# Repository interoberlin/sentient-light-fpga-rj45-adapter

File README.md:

# Lattice iCEstick adapter with four RJ-45 sockets

The adapter in this repository takes sixteen 3V3 logic level input signals,
converts them to 5V and outputs them on four RJ-45 sockets, four signals per socket,
one signal per twisted pair of an off-the-shelf CAT-5 ethernet cable.
Eight additional inputs can switch the RJ-45 sockets' LEDs on and off.

## Pictures

### Top layer

### Bottom layer

### With components

### With iCEstick

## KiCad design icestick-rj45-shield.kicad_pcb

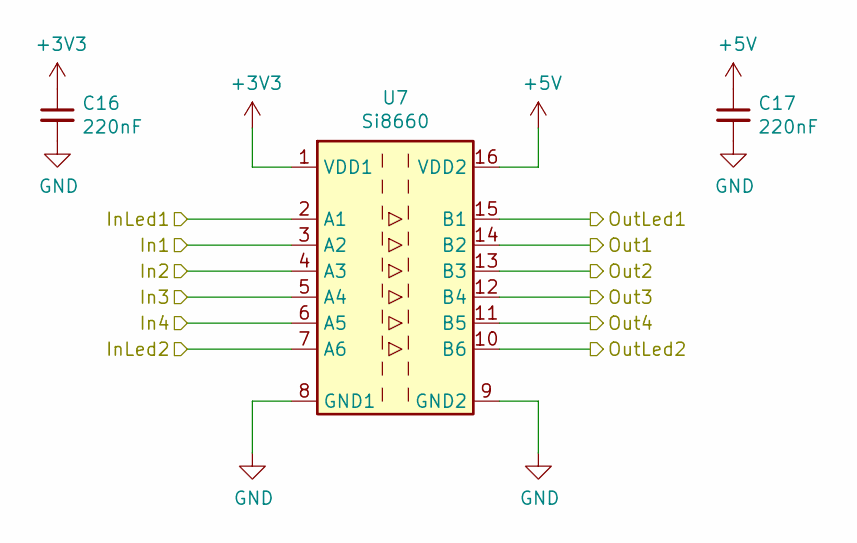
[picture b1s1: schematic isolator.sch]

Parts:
C1, C2: 220nF; C_0805_2012Metric_Pad1.15x1.40mm_HandSolder
U1: Si8660; SOIC-16_3.9x9.9mm_P1.27mm

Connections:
+3V3: C1.1, U1.1 (VDD1); also elsewhere on the board
+5V: C2.1, U1.16 (VDD2); also elsewhere on the board
/Connector 1/LED1: U1.10 (B6); also elsewhere on the board
/Connector 1/LED2: U1.15 (B1); also elsewhere on the board
/Isolator 1/Out1: U1.14 (B2); also elsewhere on the board
/Isolator 1/Out2: U1.13 (B3); also elsewhere on the board
/Isolator 1/Out3: U1.12 (B4); also elsewhere on the board
/Isolator 1/Out4: U1.11 (B5); also elsewhere on the board
/iCEstick connector/FPGA_114: U1.7 (A6); also elsewhere on the board
/iCEstick connector/FPGA_115: U1.6 (A5); also elsewhere on the board
/iCEstick connector/FPGA_116: U1.5 (A4); also elsewhere on the board
/iCEstick connector/FPGA_117: U1.4 (A3); also elsewhere on the board
/iCEstick connector/FPGA_118: U1.3 (A2); also elsewhere on the board
/iCEstick connector/FPGA_119: U1.2 (A1); also elsewhere on the board
GND: C1.2, C2.2, U1.8 (GND1), U1.9 (GND2); also elsewhere on the board

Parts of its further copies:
C12, C13, C14, C15, C16, C17: 220nF; C_0805_2012Metric_Pad1.15x1.40mm_HandSolder
U5, U6, U7: Si8660; SOIC-16_3.9x9.9mm_P1.27mm

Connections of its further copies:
+3V3: C12.1, C14.1, C16.1, U5.1 (VDD1), U6.1 (VDD1), U7.1 (VDD1); also elsewhere on the board
+5V: C13.1, C15.1, C17.1, U5.16 (VDD2), U6.16 (VDD2), U7.16 (VDD2); also elsewhere on the board
/Connector 2/LED1: U5.10 (B6); also elsewhere on the board
/Connector 2/LED2: U5.15 (B1); also elsewhere on the board
/Connector 3/LED1: U7.10 (B6); also elsewhere on the board
/Connector 3/LED2: U7.15 (B1); also elsewhere on the board
/Connector 4/LED1: U6.10 (B6); also elsewhere on the board
/Connector 4/LED2: U6.15 (B1); also elsewhere on the board
/Isolator 2/Out1: U5.14 (B2); also elsewhere on the board
/Isolator 2/Out2: U5.13 (B3); also elsewhere on the board
/Isolator 2/Out3: U5.12 (B4); also elsewhere on the board
/Isolator 2/Out4: U5.11 (B5); also elsewhere on the board
/Isolator 3/Out1: U7.14 (B2); also elsewhere on the board
/Isolator 3/Out2: U7.13 (B3); also elsewhere on the board
/Isolator 3/Out3: U7.12 (B4); also elsewhere on the board
/Isolator 3/Out4: U7.11 (B5); also elsewhere on the board
/Isolator 4/Out1: U6.14 (B2); also elsewhere on the board
/Isolator 4/Out2: U6.13 (B3); also elsewhere on the board
/Isolator 4/Out3: U6.12 (B4); also elsewhere on the board
/Isolator 4/Out4: U6.11 (B5); also elsewhere on the board
/iCEstick connector/FPGA_44: U6.7 (A6); also elsewhere on the board
/iCEstick connector/FPGA_45: U6.6 (A5); also elsewhere on the board
/iCEstick connector/FPGA_47: U6.5 (A4); also elsewhere on the board
/iCEstick connector/FPGA_48: U6.4 (A3); also elsewhere on the board
/iCEstick connector/FPGA_56: U6.3 (A2); also elsewhere on the board
/iCEstick connector/FPGA_60: U6.2 (A1); also elsewhere on the board
/iCEstick connector/FPGA_61: U7.7 (A6); also elsewhere on the board
/iCEstick connector/FPGA_62: U7.6 (A5); also elsewhere on the board
/iCEstick connector/FPGA_78: U7.3 (A2); also elsewhere on the board
/iCEstick connector/FPGA_79: U7.2 (A1); also elsewhere on the board
/iCEstick connector/FPGA_80: U5.7 (A6); also elsewhere on the board
/iCEstick connector/FPGA_81: U5.6 (A5); also elsewhere on the board
/iCEstick connector/FPGA_87: U7.4 (A3); also elsewhere on the board
/iCEstick connector/FPGA_88: U7.5 (A4); also elsewhere on the board
/iCEstick connector/FPGA_90: U5.4 (A3); also elsewhere on the board
/iCEstick connector/FPGA_91: U5.5 (A4); also elsewhere on the board
/iCEstick connector/FPGA_112: U5.3 (A2); also elsewhere on the board
/iCEstick connector/FPGA_113: U5.2 (A1); also elsewhere on the board
GND: C12.2, C13.2, C14.2, C15.2, C16.2, C17.2, U5.8 (GND1), U5.9 (GND2), U6.8 (GND1), U6.9 (GND2), U7.8 (GND1), U7.9 (GND2); also elsewhere on the board

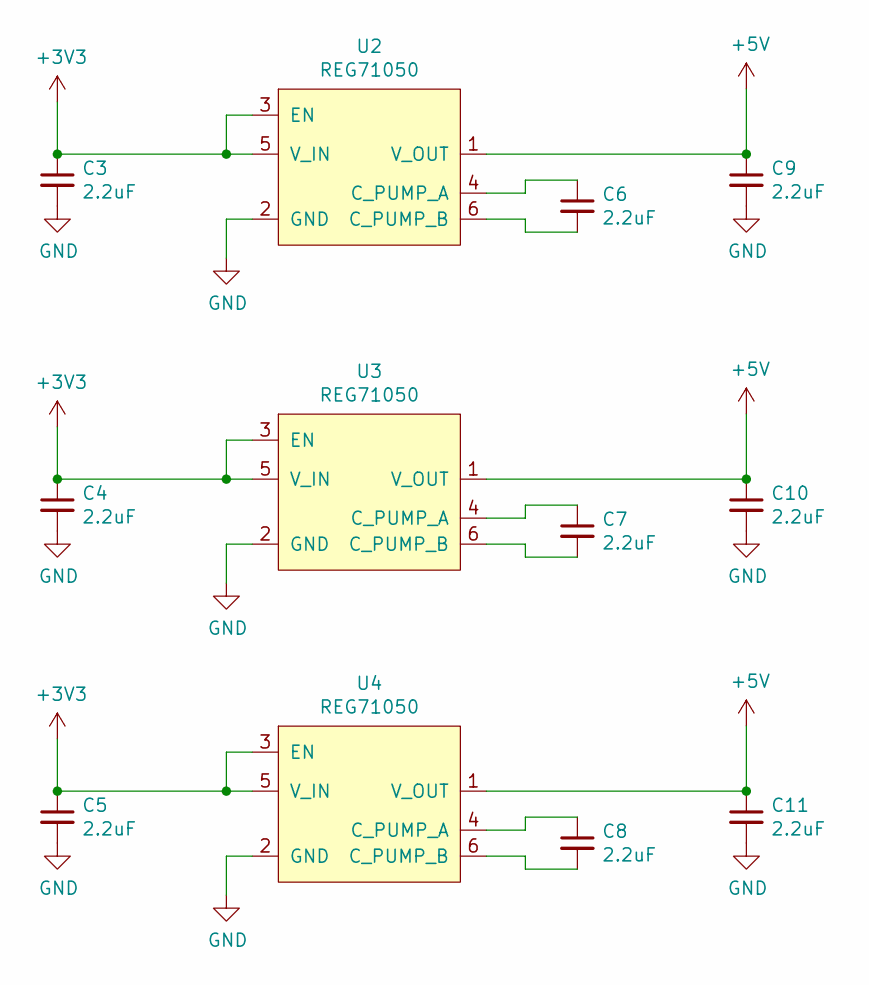
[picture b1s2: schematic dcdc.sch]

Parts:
C3, C4, C5, C6, C7, C8, C9, C10, C11: 2.2uF; C_0805_2012Metric_Pad1.15x1.40mm_HandSolder
U2, U3, U4: REG71050; SOT-23-6_Handsoldering

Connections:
+3V3: C3.1, C4.1, C5.1, U2.3 (EN), U2.5 (V_IN), U3.3 (EN), U3.5 (V_IN), U4.3 (EN), U4.5 (V_IN); also elsewhere on the board
+5V: C9.1, C10.1, C11.1, U2.1 (V_OUT), U3.1 (V_OUT), U4.1 (V_OUT); also elsewhere on the board
GND: C3.2, C4.2, C5.2, C9.2, C10.2, C11.2, U2.2 (GND), U3.2 (GND), U4.2 (GND); also elsewhere on the board
unnamed: C6.1, U2.4 (C_PUMP_A)
unnamed: C6.2, U2.6 (C_PUMP_B)
unnamed: C7.1, U3.4 (C_PUMP_A)
unnamed: C7.2, U3.6 (C_PUMP_B)
unnamed: C8.1, U4.4 (C_PUMP_A)
unnamed: C8.2, U4.6 (C_PUMP_B)

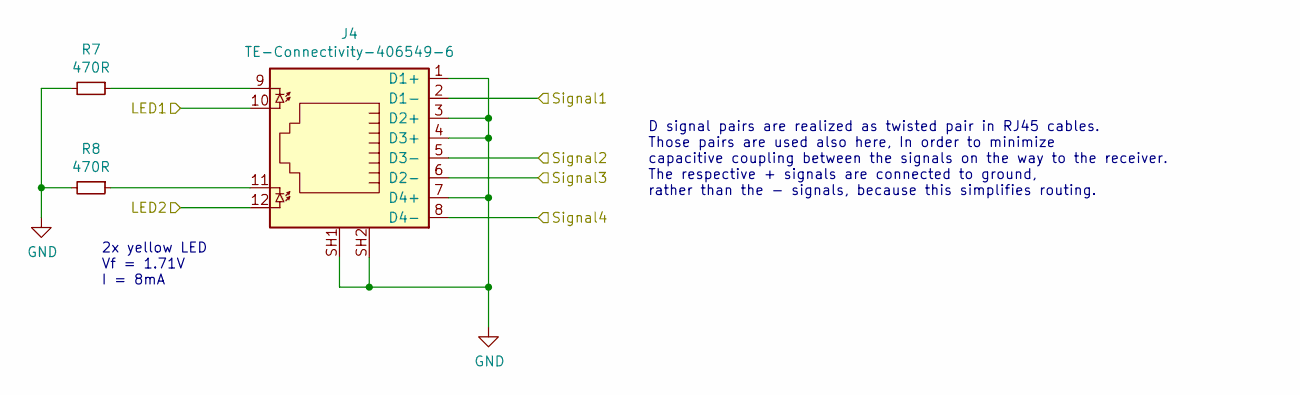
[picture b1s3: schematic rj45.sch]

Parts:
J2: TE-Connectivity-406549-6
R1, R2: 470R; R_0805_2012Metric_Pad1.15x1.40mm_HandSolder

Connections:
/Connector 2/LED1: J2.10; also elsewhere on the board
/Connector 2/LED2: J2.12; also elsewhere on the board
/Isolator 2/Out1: J2.8 (D4-); also elsewhere on the board
/Isolator 2/Out2: J2.6 (D2-); also elsewhere on the board
/Isolator 2/Out3: J2.2 (D1-); also elsewhere on the board
/Isolator 2/Out4: J2.5 (D3-); also elsewhere on the board
GND: J2.1 (D1+), J2.3 (D2+), J2.4 (D3+), J2.7 (D4+), J2.SH1, J2.SH2, R1.2, R2.2; also elsewhere on the board

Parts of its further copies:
J1, J3, J4: TE-Connectivity-406549-6
R3, R4, R5, R6, R7, R8: 470R; R_0805_2012Metric_Pad1.15x1.40mm_HandSolder

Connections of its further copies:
/Connector 1/LED1: J1.10; also elsewhere on the board
/Connector 1/LED2: J1.12; also elsewhere on the board
/Connector 3/LED1: J3.10; also elsewhere on the board
/Connector 3/LED2: J3.12; also elsewhere on the board
/Connector 4/LED1: J4.10; also elsewhere on the board
/Connector 4/LED2: J4.12; also elsewhere on the board
/Isolator 1/Out1: J1.8 (D4-); also elsewhere on the board
/Isolator 1/Out2: J1.6 (D2-); also elsewhere on the board
/Isolator 1/Out3: J1.2 (D1-); also elsewhere on the board
/Isolator 1/Out4: J1.5 (D3-); also elsewhere on the board
/Isolator 3/Out1: J3.8 (D4-); also elsewhere on the board
/Isolator 3/Out2: J3.6 (D2-); also elsewhere on the board
/Isolator 3/Out3: J3.2 (D1-); also elsewhere on the board
/Isolator 3/Out4: J3.5 (D3-); also elsewhere on the board
/Isolator 4/Out1: J4.8 (D4-); also elsewhere on the board
/Isolator 4/Out2: J4.6 (D2-); also elsewhere on the board
/Isolator 4/Out3: J4.2 (D1-); also elsewhere on the board
/Isolator 4/Out4: J4.5 (D3-); also elsewhere on the board
GND: J1.1 (D1+), J1.3 (D2+), J1.4 (D3+), J1.7 (D4+), J1.SH1, J1.SH2, J3.1 (D1+), J3.3 (D2+), J3.4 (D3+), J3.7 (D4+), J3.SH1, J3.SH2, J4.1 (D1+), J4.3 (D2+), J4.4 (D3+), J4.7 (D4+), J4.SH1, J4.SH2, R3.2, R4.2, R5.2, R6.2, R7.2, R8.2; also elsewhere on the board
unnamed: J3.9, R5.1
unnamed: J3.11, R6.1
unnamed: J4.9, R7.1
unnamed: J4.11, R8.1

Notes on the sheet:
2x yellow LED Vf = 1.71V I = 8mA
D signal pairs are realized as twisted pair in RJ45 cables. Those pairs are used also here, In order to minimize capacitive coupling between the signals on the way to the receiver. The respective + signals are connected to ground, rather than the - signals, because this simplifies routing.

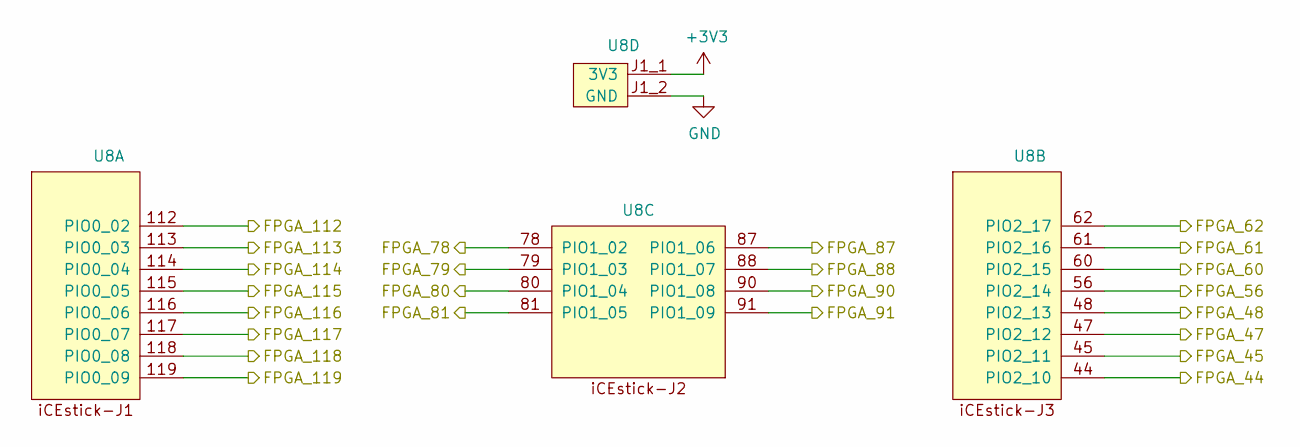
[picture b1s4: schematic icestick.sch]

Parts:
U8: iCEstick

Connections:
+3V3: U8.J1_1 (3V3), U8.J2_6 (3V3), U8.J2_12 (3V3), U8.J3_1 (3V3); also elsewhere on the board
/iCEstick connector/FPGA_44: U8.44 (PIO2_10); also elsewhere on the board
/iCEstick connector/FPGA_45: U8.45 (PIO2_11); also elsewhere on the board
/iCEstick connector/FPGA_47: U8.47 (PIO2_12); also elsewhere on the board
/iCEstick connector/FPGA_48: U8.48 (PIO2_13); also elsewhere on the board
/iCEstick connector/FPGA_56: U8.56 (PIO2_14); also elsewhere on the board
/iCEstick connector/FPGA_60: U8.60 (PIO2_15); also elsewhere on the board
/iCEstick connector/FPGA_61: U8.61 (PIO2_16); also elsewhere on the board
/iCEstick connector/FPGA_62: U8.62 (PIO2_17); also elsewhere on the board
/iCEstick connector/FPGA_78: U8.78 (PIO1_02); also elsewhere on the board
/iCEstick connector/FPGA_79: U8.79 (PIO1_03); also elsewhere on the board
/iCEstick connector/FPGA_80: U8.80 (PIO1_04); also elsewhere on the board
/iCEstick connector/FPGA_81: U8.81 (PIO1_05); also elsewhere on the board
/iCEstick connector/FPGA_87: U8.87 (PIO1_06); also elsewhere on the board
/iCEstick connector/FPGA_88: U8.88 (PIO1_07); also elsewhere on the board
/iCEstick connector/FPGA_90: U8.90 (PIO1_08); also elsewhere on the board
/iCEstick connector/FPGA_91: U8.91 (PIO1_09); also elsewhere on the board
/iCEstick connector/FPGA_112: U8.112 (PIO0_02); also elsewhere on the board
/iCEstick connector/FPGA_113: U8.113 (PIO0_03); also elsewhere on the board
/iCEstick connector/FPGA_114: U8.114 (PIO0_04); also elsewhere on the board
/iCEstick connector/FPGA_115: U8.115 (PIO0_05); also elsewhere on the board
/iCEstick connector/FPGA_116: U8.116 (PIO0_06); also elsewhere on the board
/iCEstick connector/FPGA_117: U8.117 (PIO0_07); also elsewhere on the board
/iCEstick connector/FPGA_118: U8.118 (PIO0_08); also elsewhere on the board
/iCEstick connector/FPGA_119: U8.119 (PIO0_09); also elsewhere on the board
GND: U8.J1_2 (GND), U8.J2_5 (GND), U8.J2_11 (GND), U8.J3_2 (GND); also elsewhere on the board

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
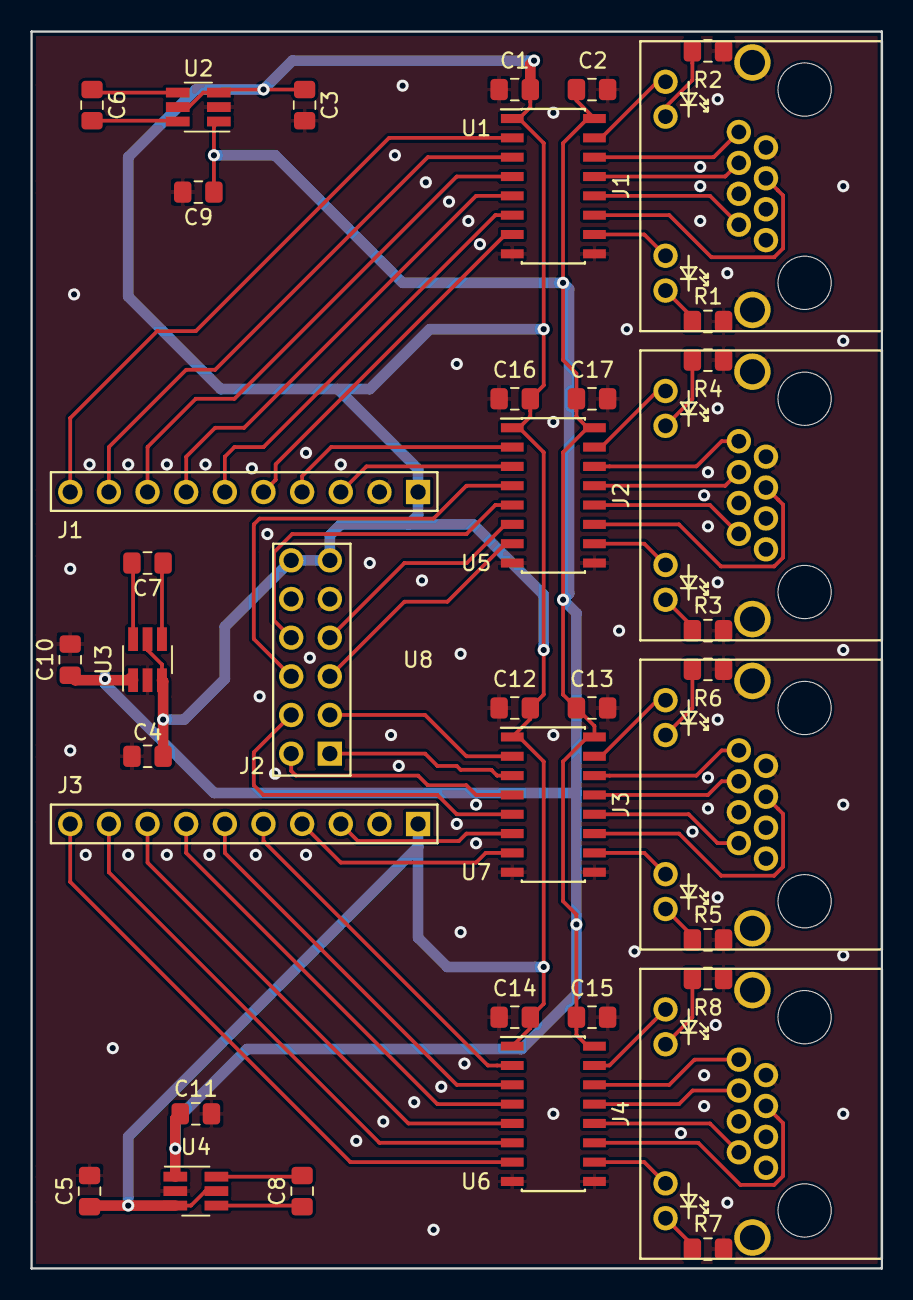
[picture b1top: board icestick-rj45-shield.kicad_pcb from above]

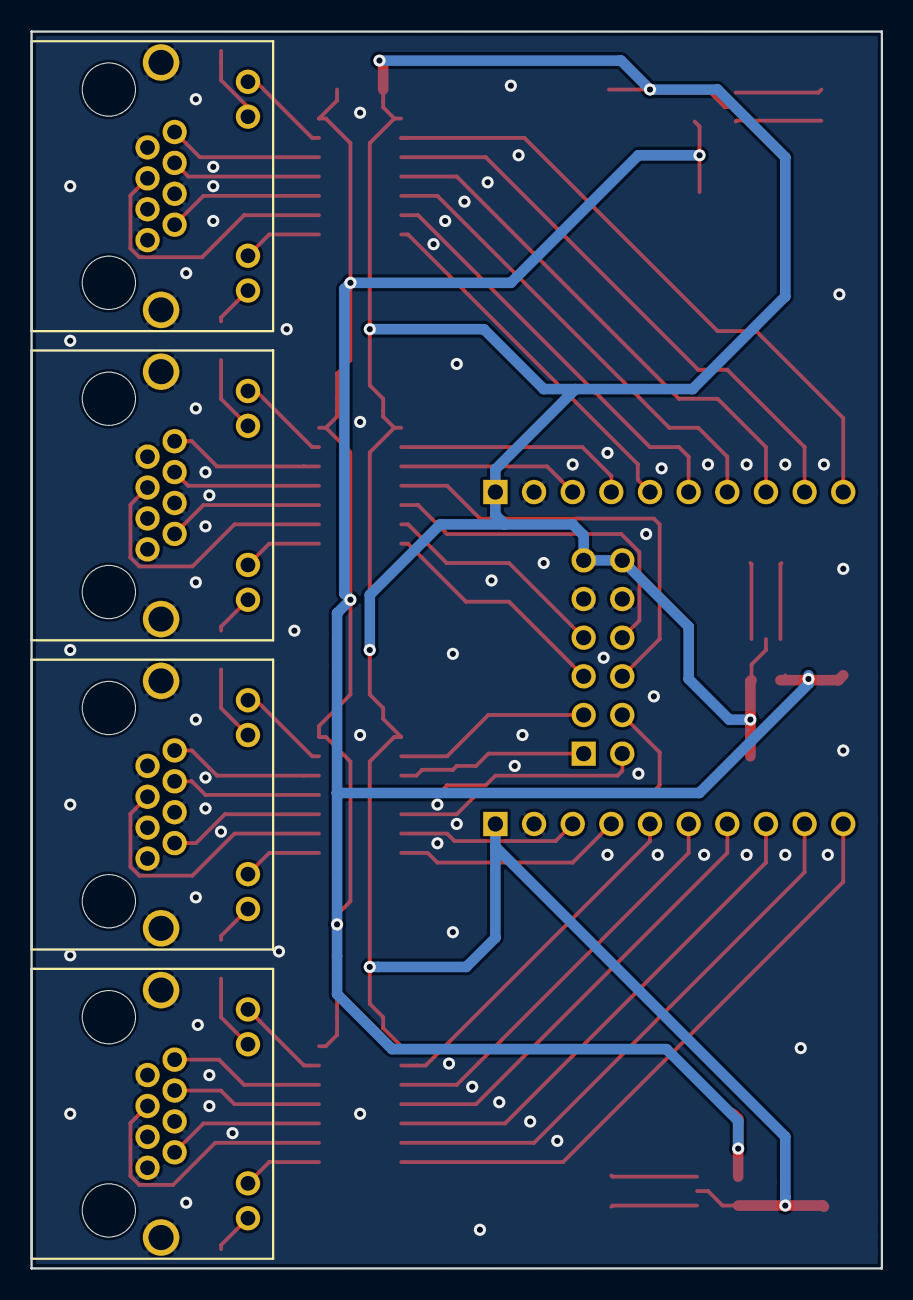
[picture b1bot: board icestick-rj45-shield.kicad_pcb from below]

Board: 2 copper layers, 55.9 x 81.3 mm, 37 parts (4 on the bottom side), 65 nets.

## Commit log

2018-10-21 Created empty KiCad 5.0 project
2018-10-21 Added iCEstick schematic in folder doc/
2018-10-21 icestick.sch: Added headers J1 and J3
2018-10-21 Fixed sheet relations (no separate projects but sub-sheets)
2018-10-21 Added library for project specific symbols
2018-10-21 Added isolators and RJ-45 connectors
2018-10-21 Added Texas Instruments REG710xx charge pump IC datasheet
2018-10-21 Added charge pump IC REG71050
2018-10-21 Added symbol library table for my symbol library
2018-10-21 Assigned footprints
2018-10-21 Began layouting
2018-10-23 Continued layouting
2018-10-24 Fixed iCEstick header distance
2018-10-24 Routed all the signals
2018-10-25 PCB: Added a couple of GND vias
2018-11-05 Switched to Si8660 isolator and changed RJ-45 connector
2018-11-06 Updated RJ45 symbol and corresponding signal names
2018-11-10 Began redesigning with Si8660
2018-11-18 Finished layout with 4x Si8660
2018-11-18 Moved PCB outline measures to Drawings layer
2018-11-18 Exported fabrication files (Gerber)
2018-11-27 Added my KiCad libraries as submodule
2018-11-29 Added fotos of v1.0
2018-11-29 Added README.md with PCB pictures
2019-03-09 CERN Open Hardware Licence v1.2
2019-03-16 Added schematic PDF, 3d rendering and STEP model
2019-03-16 Fixed broken image links
